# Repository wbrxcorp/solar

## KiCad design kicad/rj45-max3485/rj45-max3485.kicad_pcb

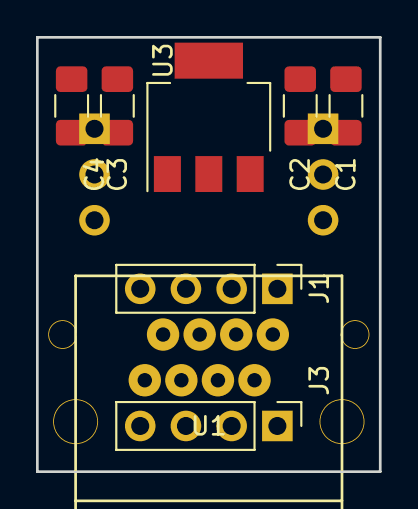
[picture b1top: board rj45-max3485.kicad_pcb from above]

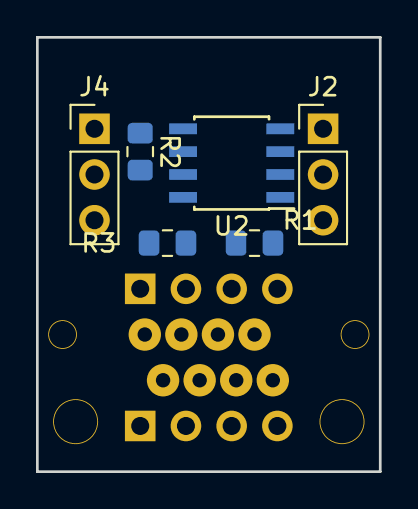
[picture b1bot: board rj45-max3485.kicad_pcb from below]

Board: 2 copper layers, 19.1 x 24.1 mm, 14 parts (6 on the bottom side), 8 nets, no tracks yet.

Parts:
C1, C4: 0.1uF; C_1206_3216Metric_Pad1.42x1.75mm_HandSolder
C2, C3: 10uF; C_1206_3216Metric_Pad1.42x1.75mm_HandSolder
J1, J3: Conn_01x04; PinHeader_1x04_P2.54mm_Vertical
J2, J4: Conn_01x03; PinHeader_1x03_P2.54mm_Vertical
R1, R3: 20k; R_0805_2012Metric_Pad1.15x1.40mm_HandSolder
R2: 120; R_0805_2012Metric_Pad1.15x1.40mm_HandSolder
U1: 7810-8P8C
U2: MAX3485; SOIC-8_3.9x4.9mm_P1.27mm
U3: AMS1117-3.3; SOT-223-3_TabPin2

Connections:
+3V3: C3.1, C4.1, J4.2, R3.2, U2.8, U3.2
/A: J1.3, J3.3, R2.1, R3.1, U1.5, U1.6, U2.6
/B: J1.2, J3.2, R1.2, R2.2, U1.3, U1.4, U2.7
/RTS: J2.3, U2.2, U2.3
/RX: J2.2, U2.1
/TX: J2.1, U2.4
GND: C1.2, C2.2, C3.2, C4.2, J1.4, J3.4, J4.3, R1.1, U1.7, U1.8, U2.5, U3.1
VCC: C1.1, C2.1, J1.1, J3.1, J4.1, U1.1, U1.2, U3.3

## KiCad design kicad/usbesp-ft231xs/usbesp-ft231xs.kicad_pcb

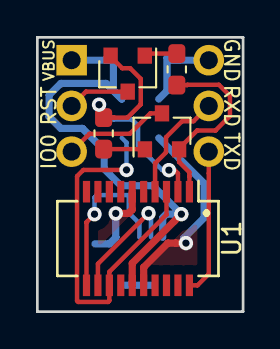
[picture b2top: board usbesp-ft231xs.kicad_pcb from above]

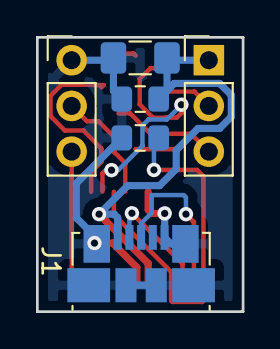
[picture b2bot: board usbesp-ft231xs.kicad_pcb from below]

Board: 2 copper layers, 11.4 x 15.2 mm, 11 parts (6 on the bottom side), 13 nets.

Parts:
C1, C3: 0.1uF; C_0805_2012Metric_Pad1.15x1.40mm_HandSolder
C2: 10uF; C_1206_3216Metric_Pad1.42x1.75mm_HandSolder
J1: USB_B_Micro; USB_Micro-B_Molex_47346-0001
J2, J3: Conn_01x06; PinHeader_1x03_P2.54mm_Vertical
Q1, Q2: S9013; SOT-23
R1, R2: 10K; R_0603_1608Metric_Pad1.05x0.95mm_HandSolder
U1: FT231XS; SSOP-20_3.9x8.7mm_P0.635mm

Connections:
/3v3: C3.1, U1.3, U1.13
/USBDM: J1.2, U1.12
/USBDP: J1.3, U1.11
DTR: Q1.2, R2.1, U1.1
GND: C1.2, C2.2, C3.2, J1.5, J1.6, J3.1, U1.6, U1.16
IO0: J2.3, Q1.3
unnamed: Q1.1, R1.2
unnamed: Q2.1, R2.2
RESET: J2.2, Q2.3
RTS: Q2.2, R1.1, U1.2
RXD: J3.2, U1.4
TXD: J3.3, U1.20
VBUS: C1.1, C2.1, J1.1, J2.1, U1.15

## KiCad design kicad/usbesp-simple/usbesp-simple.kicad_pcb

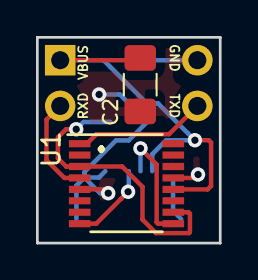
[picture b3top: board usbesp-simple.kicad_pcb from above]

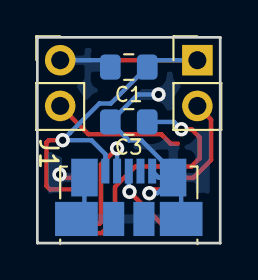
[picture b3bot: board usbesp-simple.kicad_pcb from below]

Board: 2 copper layers, 10.2 x 11.4 mm, 7 parts (5 on the bottom side), 7 nets.

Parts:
C1, C3: 0.1uF; C_0805_2012Metric_Pad1.15x1.40mm_HandSolder
C2: 10uF; C_1206_3216Metric_Pad1.42x1.75mm_HandSolder
J1: USB_B_Micro; USB_Micro-B_Molex_47346-0001
J2, J3: Conn_01x02; PinHeader_1x02_P2.54mm_Vertical
U1: FT230XS; SSOP-16_3.9x4.9mm_P0.635mm

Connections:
/3V3: C3.1, U1.3, U1.10
/RXD: J2.2, U1.4
/TXD: J3.2, U1.1
/USBDM: J1.2, U1.9
/USBDP: J1.3, U1.8
/VBUS: C1.1, C2.1, J1.1, J2.1, U1.12
GND: C1.2, C2.2, C3.2, J1.5, J1.6, J3.1, U1.5, U1.13

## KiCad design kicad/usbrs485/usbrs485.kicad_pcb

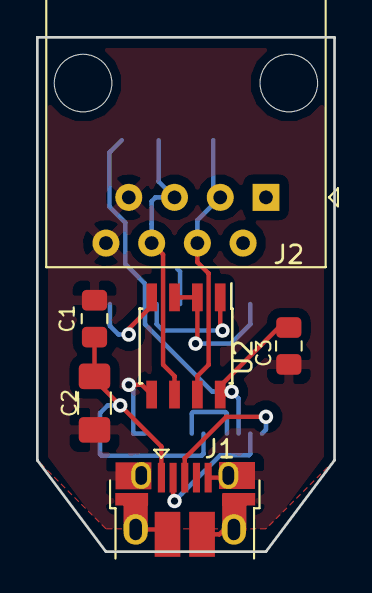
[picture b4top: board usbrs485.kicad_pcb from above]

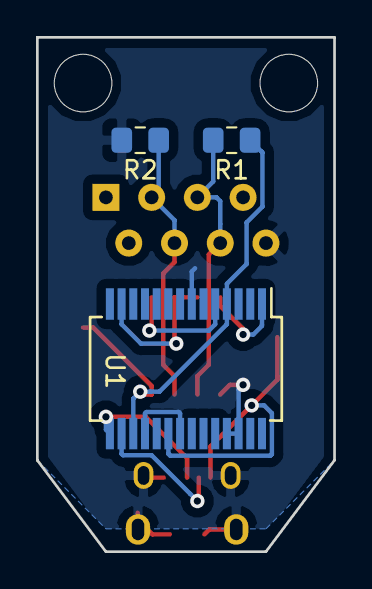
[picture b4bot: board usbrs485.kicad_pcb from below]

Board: 2 copper layers, 16.5 x 28.6 mm, 9 parts (3 on the bottom side), 10 nets.

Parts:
C1, C3: 0.1uF; C_0805_2012Metric_Pad1.15x1.40mm_HandSolder
C2: 10uF; C_1206_3216Metric_Pad1.42x1.75mm_HandSolder
J1: USB_B_Micro; USB_Micro-B_Amphenol_10103594-0001LF_Horizontal
J2: RJ45; RJ45_Amphenol_54602-x08_Horizontal
R1, R2: 20K; R_0805_2012Metric_Pad1.15x1.40mm_HandSolder
U1: FT232RL; SSOP-28_5.3x10.2mm_P0.65mm
U2: MAX3485; SOIC-8_3.9x4.9mm_P1.27mm

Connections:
/3v3: C3.1, R1.1, U1.4, U1.17, U2.8
/A: J2.5, J2.6, R1.2, U2.6
/B: J2.3, J2.4, R2.1, U2.7
/DE: U1.13, U2.2, U2.3
/RXD: U1.5, U2.1
/TXD: U1.1, U2.4
/USBDM: J1.2, U1.16
/USBDP: J1.3, U1.15
/VBUS: C1.1, C2.1, J1.1, U1.20
GND: C1.2, C2.2, C3.2, J1.5, J1.6, J2.7, J2.8, R2.2, U1.7, U1.18, U1.21, U1.25, U1.26, U2.5
